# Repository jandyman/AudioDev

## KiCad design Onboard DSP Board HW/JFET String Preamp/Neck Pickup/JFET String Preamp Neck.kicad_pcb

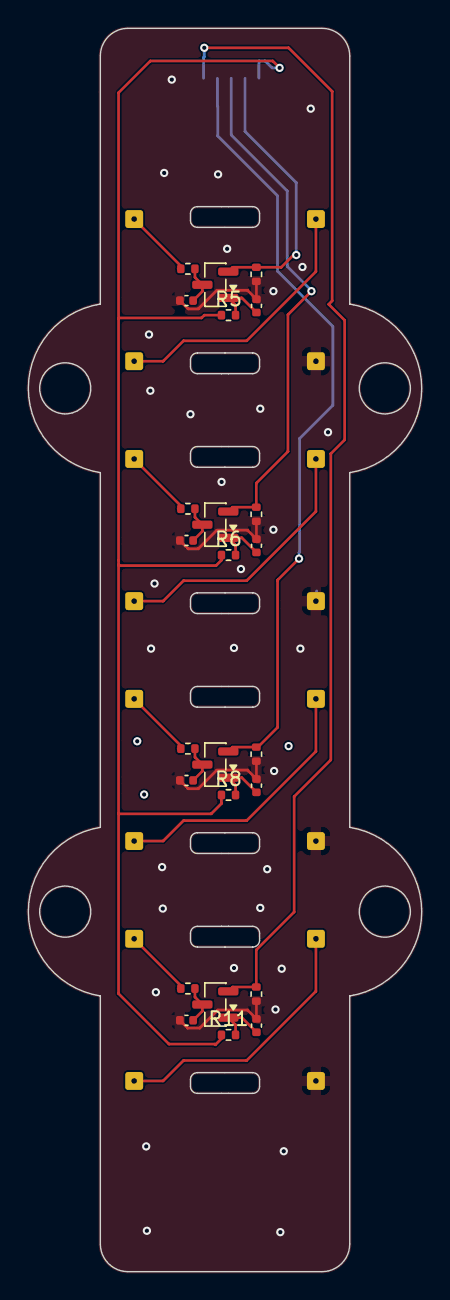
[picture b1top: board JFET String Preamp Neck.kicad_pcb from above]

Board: 2 copper layers, 28.4 x 89.9 mm, 41 parts (1 on the bottom side), 22 nets.

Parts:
C2, C5, C7, C9: 100nF; C_0402_1005Metric
C3, C4, C6, C8: 100pF; C_0402_1005Metric
J1, J5, J10, J14: Input; Magnet Wire THT
J2, J3, J4, J6, J7, J8, J11, J12, J13, J15, J16, J17: Magnet Wire THT
J9: JST_SH_SM06B-SRSS-TB_1x06-1MP_P1.00mm_Horizontal
Q1, Q2, Q3, Q4: MMBF201; SOT-23
R1, R4, R9, R12: 2.2K; R_0402_1005Metric
R2, R3, R7, R10: 1K; R_0402_1005Metric
R5, R6, R8, R11: 100; R_0402_1005Metric

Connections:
/SIngle FET preamp1/Output: J9.3, Q2.2 (S), R4.1
/SIngle FET preamp2/Output: J9.4, Q3.2 (S), R9.1
/SIngle FET preamp3/Output: J9.5, Q4.2 (S), R12.1
/SIngle FET preamp/3.7V: J9.1, R5.1, R6.1, R8.1, R11.1
/SIngle FET preamp/Output: J9.2, Q1.2 (S), R1.1
GND: C2.1, C3.1, C4.1, C5.1, C6.1, C7.1, C8.1, C9.1, J2.1 (Pin_1_1), J8.1 (Pin_1_1), J9.6, J13.1 (Pin_1_1), J17.1 (Pin_1_1), R1.2, R4.2, R9.2, R12.2
unnamed: J1.1 (Pin_1_1), R2.1
unnamed: J3.1 (Pin_1_1), J4.1 (Pin_1_1)
unnamed: J5.1 (Pin_1_1), R3.1
unnamed: J6.1 (Pin_1_1), J7.1 (Pin_1_1)
unnamed: J10.1 (Pin_1_1), R7.1
unnamed: J11.1 (Pin_1_1), J12.1 (Pin_1_1)
unnamed: J14.1 (Pin_1_1), R10.1
unnamed: J15.1 (Pin_1_1), J16.1 (Pin_1_1)
unnamed: C2.2, Q1.1 (D), R5.2
unnamed: C3.2, Q1.3 (G), R2.2
unnamed: C5.2, Q2.1 (D), R6.2
unnamed: C4.2, Q2.3 (G), R3.2
unnamed: C7.2, Q3.1 (D), R8.2
unnamed: C6.2, Q3.3 (G), R7.2
unnamed: C9.2, Q4.1 (D), R11.2
unnamed: C8.2, Q4.3 (G), R10.2

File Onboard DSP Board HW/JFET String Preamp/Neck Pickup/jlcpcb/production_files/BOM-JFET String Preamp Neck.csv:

Comment,Designator,Footprint,LCSC,Quantity
100nF,C9,C_0402_1005Metric,,1
100,R8,R_0402_1005Metric,,1
100,R6,R_0402_1005Metric,,1
100nF,C5,C_0402_1005Metric,,1
100nF,C3,C_0402_1005Metric,,1
2.2K,R4,R_0402_1005Metric,,1
100nF,C4,C_0402_1005Metric,,1
MMBF201,Q4,SOT-23,,1
1K,R10,R_0402_1005Metric,,1
100,R5,R_0402_1005Metric,,1
MMBF201,Q2,SOT-23,,1
MMBF201,Q3,SOT-23,,1
100nF,C7,C_0402_1005Metric,,1
1K,R3,R_0402_1005Metric,,1
MMBF201,Q1,SOT-23,,1
1K,R7,R_0402_1005Metric,,1
1K,R2,R_0402_1005Metric,,1
100nF,C6,C_0402_1005Metric,,1
100nF,C2,C_0402_1005Metric,,1
2.2K,R1,R_0402_1005Metric,,1
2.2K,R9,R_0402_1005Metric,,1
100,R11,R_0402_1005Metric,,1
100nF,C8,C_0402_1005Metric,,1
2.2K,R12,R_0402_1005Metric,,1
